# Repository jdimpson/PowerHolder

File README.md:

# PowerHolder PCB

Another variation of the AdaFruit PowerBoost 1000C (https://www.adafruit.com/product/2465) adapted for Raspberry Pi Zero. This is functionally similar to the PowerBoard (https://github.com/jdimpson/PowerBoard), but this time, with a side car that holds an entire 18650 Lithium Ion cell. As with PowerBoard, adds a  schottkey diode and programmable tactile button and LED and patches the Low Battery (LBO) signal to the Pi via a level shifter.

Also significant, this board lets you choose whether you want to pick-and-place and then reflow your own electronic components, or just go out and buy a PowerBoost 1000C from AdaFruit. You still have to solder on a diode, the battery holder clips, and (if you want them) the signal LED, programmable button, enable switch, and the level shifting mosfet for the LBO signal. But most of the fiddly parts, notably the U1 and U2 controller chips, you can use from the standard AdaFruit product. Just solder the board into place in the matching header holes with the male header pins they provide, or get some female headers too (that option makes clearance problems).

Note: when you solder a Powerboost in place, it's JST socket won't be accessible. Presumably this is okay because the battery sidecar is right there. The drawback is that the sidecar assumes your 18650 cell has exposed electrical contact on each of the opposing ends of the cell cylinder, rather than wires or tabs spot-welded onto the battery then brought out to a JST or similar connector. You could cut off the connector and solder battery wires onto the BAT and GND pins of the header if you want, or to the plus and minus pads of the battery clips.

Other things worthy of note:
- The MicroUSB connector is not the same foot print as AdaFruit uses in their PowerBoost, because I couldn't figure out which part which part number it was. My chosen replacement still has the through-hole-ish studs for physical reinforcement like Adafruit uses, but the footprints are incompatible.
- A BOM export is provided, which contains Digi-Key part numbers as wellas vendor part numbers.
- Python software that works with the LBO signal, button, and LED are available in the [RPiIoT](https://github.com/jdimpson/RPiIoT) repo. You don't have to use this software to benefit from this board, but you do want to monitor GPIO26/Phy37 because when it goes low, the battery voltage has dropped near the point where the charge controller will soon switch off power.
- Auxillary header is provided for USB/5VDC electrical input if you don't want to use MicroUSB.
- Auxillary header is provided for boosted 5VDC electrical output if you want to power something else with this board (in addition to, or instead of, an RPi Zero). NOte this auxillary output is not protected by the schottkey diode. This is analogous to the USB output header that the original PowerBoost 1000C provides, although the sense resistors used to indicate availability of > 500 mA have been removed.
- Unlike most RPi Zero daughter boards (hats, although this does not qualify as a hat because it has no EEPROM and is larger than the starndard board footprint), this board makes more sense to mount _underneath_ the RPi Zero. You'd do this by soldering female headers into the bottom of the RPi Zero, or better yet, the stacking headers like this: https://www.adafruit.com/product/2223. THen put male headers on the PowerHolder, stack the Zero on the PowerHolder, and then put whatever you want on top of the Zero as normal. You can also put the PowerHolder on top of the Zero (with or without stacking header) but the battery placement make the whole thing look weird to me.
- The PowerBoost 1000C can source about 1 Amp of current. This is plenty for an RPi Zero, with enough to spare for a camera and another hat of some type. It might even be enough to power an RPi 1 plus or 2, and it will boot a 3 but you'll likely see warnings abou undercurrent conditions. It won't run a 3+ or a 4 (well, they say the 4 will adjust power usage, but I don't know if it adapts to as low as an amp, and I wouldn't want to waste a 4 in a low power configuration anyways). It also won't run a servo or other motor, because they seem to have such rapid current draw that the RPi Zero will reboot regularly, presumably due to voltage drop.

Changes 
- v1.01: Changed MicroUSB connector to one I can find on Digikey; move battery terminals further from RPi header; used thinner/narrower battery holder; add more plus and minus signs (near battery and the USB input header); improve location of component names; added circles around all used pins (squares around GND). 

TODO 
- Since the battery is now onboard, Figure out how to use NTC resistor ("THERM" in the schematic) to monitor battery temperature. This board provides a header to place the NTC, although I haven't experimented with it so have no recommendation for part to use.

Raspberry Pi Pins used:

- GPIO17/Phy11 is connected to a momentary / tactile switch. Available for arbitrary software control (typically running my powerboard.py and associated code from the [RPiIoT](https://github.com/jdimpson/RPiIoT) repo).
- GPIO27/Phy13 is connected to a resistor and then an LED. Available for arbitrary software control (e.g. flashing to show grace period, and typically running my powerboard.py and associated code from the [RPiIoT](https://github.com/jdimpson/RPiIoT) repo).
- GPIO26/Phy37 is connected to via transistor and appropriate hold up resistor to the LBO signal of the PowerBoost circuit. This is how the Raspberry Pi knows to shut down. The signal is held at battery level (but level shifted to 3.3 V before hitting the RPi) until the Li Ion battery level drops below 3.4VDC (or maybe it's 3.2V, I forget) at which point the LBO signal drops to ground. This tells the software on the RPi to do a graceful shutdown.

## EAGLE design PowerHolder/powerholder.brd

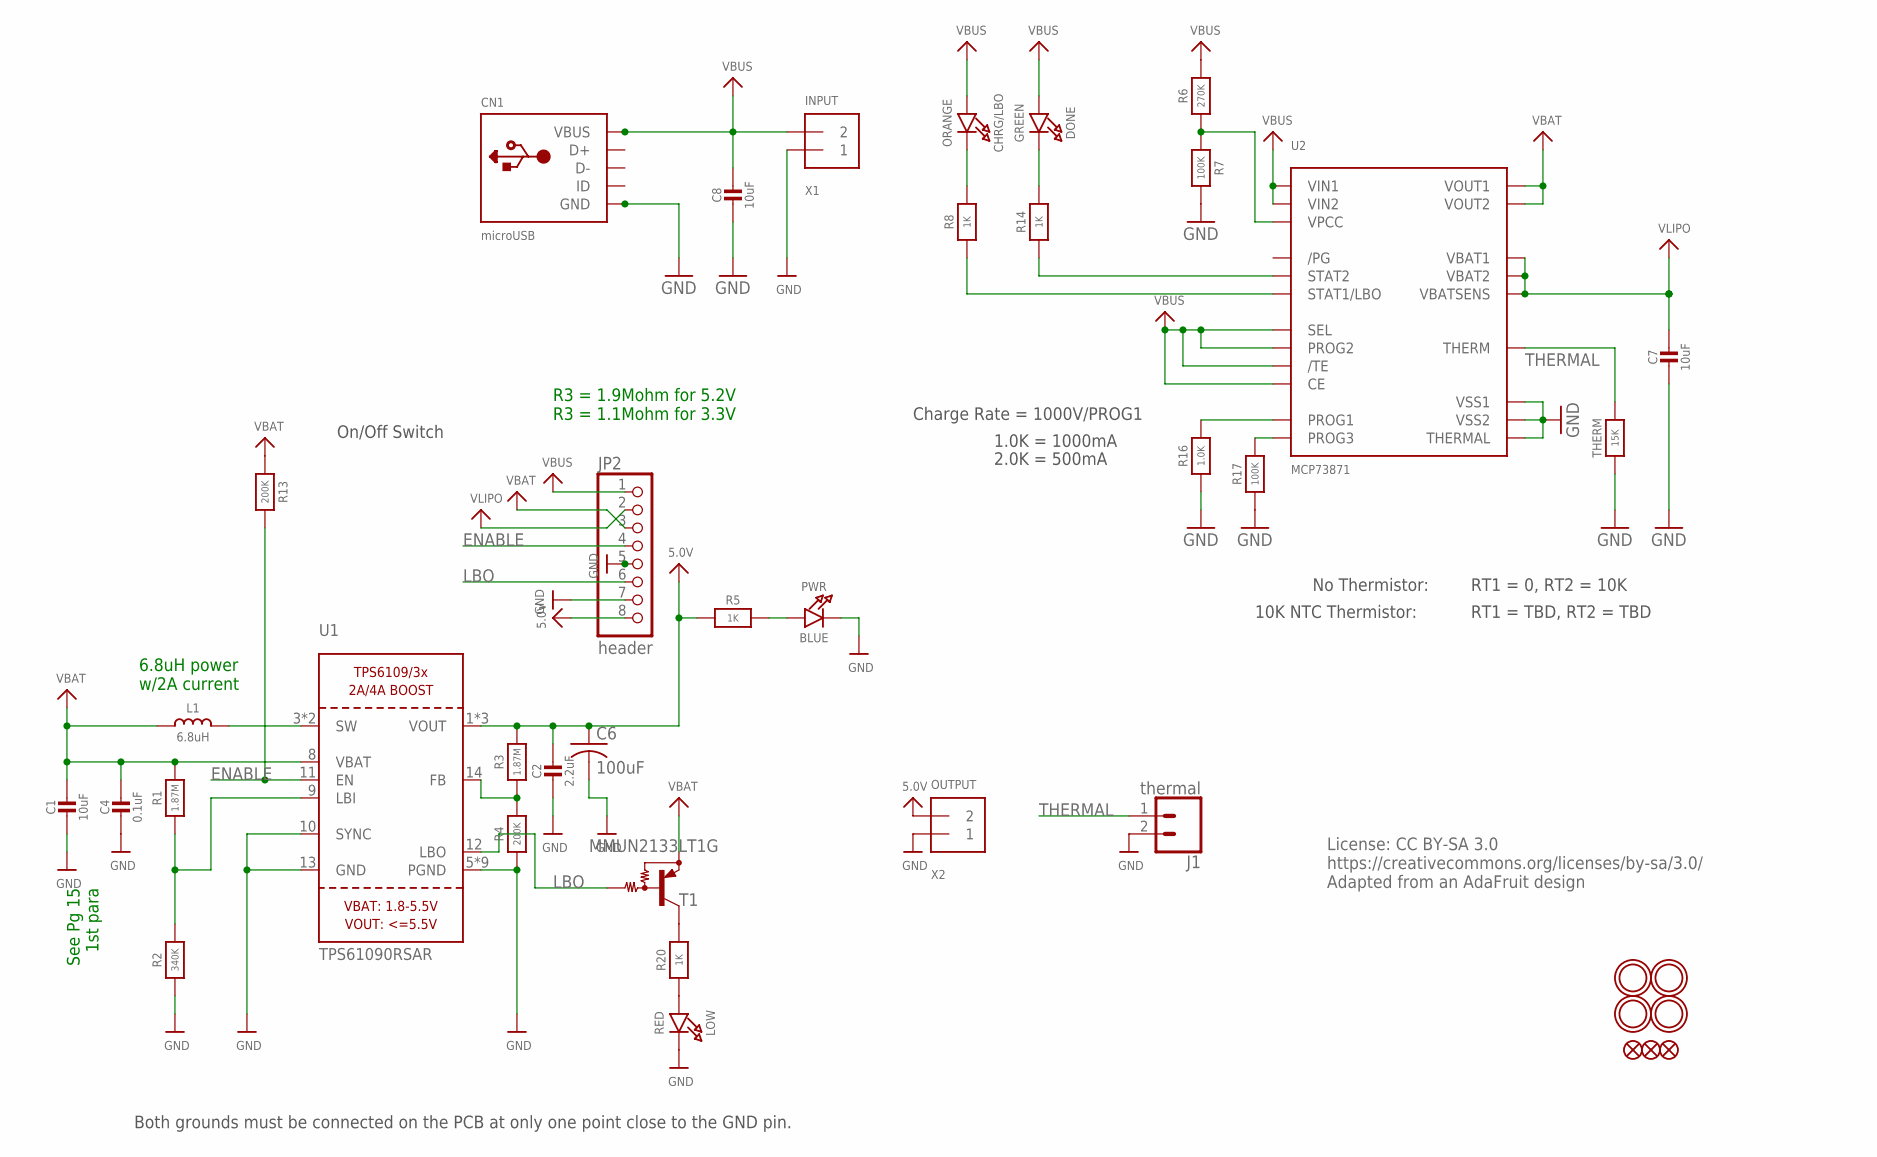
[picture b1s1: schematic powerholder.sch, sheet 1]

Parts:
C1, C7, C8: 10uF; 0805-NO@1
C2: 2.2uF; 0805-NO@1
C4: 0.1uF; 0805_10MGAP
C6: 100uF; C1210
CHRG/LBO: ORANGE; CHIPLED_0805_NOOUTLINE
CN1: microUSB; 4UCONN_20329
DONE: GREEN; CHIPLED_0805_NOOUTLINE
FID1, FID2, FID3: FIDUCIAL""; FIDUCIAL_1MM
J1: thermal; 1X02_NO_SILK
JP2: header; 1X08_ROUND
L1: 6.8uH; INDUCTOR_5X5MM_TDK_VLC5045
LOW: RED; CHIPLED_0805_NOOUTLINE
PWR: BLUE; CHIPLED_0805_NOOUTLINE
R1: 1.87M; _0805MP
R2: 340K; _0805MP
R3: 1.87M; 0805-NO
R4, R13: 200K; 0805-NO
R5, R8, R14, R20: 1K; 0805-NO
R6: 270K; 0805-NO
R7, R17: 100K; 0805-NO
R16: 1.0K; 0805-NO
T1: MMUN2133LT1G; SC59-BEC
THERM: 15K; 0805-NO
U1: TPS61090RSAR; PVQFN-16
U2: MCP73871; QFN20_4MM
U$10, U$11, U$50, U$51: MOUNTINGHOLE2.5; MOUNTINGHOLE_2.5_PLATED
X1: INPUT; TERMBLOCK_1X2-3.5MM
X2: OUTPUT; TERMBLOCK_1X2-3.5MM

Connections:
5.0V: C2.1, C6.1, JP2.8, R3.2, R5.1, U1.1 (VOUT), U1.15 (VOUT), U1.16 (VOUT), X2.2; also elsewhere on the board
ENABLE: JP2.4, R13.2, U1.11 (EN); also elsewhere on the board
GND: C1.2, C2.2, C4.2, C6.2, C7.2, C8.2, CN1.BASE@1 (GND), CN1.BASE@2 (GND), CN1.GND, CN1.SPRT@1 (GND), CN1.SPRT@2 (GND), CN1.SPRT@3 (GND), CN1.SPRT@4 (GND), J1.2, JP2.5, JP2.7, LOW.C, PWR.C, R2.1, R4.1, R7.2, R16.1, R17.1, THERM.1, U1.5 (PGND), U1.6 (PGND), U1.7 (PGND), U1.10 (SYNC), U1.13 (GND), U1.P$18 (PGND), U1.P$19 (PGND), U1.P$20 (PGND), U1.P$21 (PGND), U1.P$22 (PGND), U1.THERMAL (PGND), U2.P$10 (VSS1), U2.P$11 (VSS2), U2.P$21 (THERMAL), X1.1, X2.1; also elsewhere on the board
LBO: JP2.6, T1.B, U1.12 (LBO); also elsewhere on the board
unnamed: L1.P$2 (2), U1.3 (SW), U1.4 (SW)
unnamed: LOW.A, R20.1
unnamed: R1.1, R2.2, U1.9 (LBI)
unnamed: PWR.A, R5.2
unnamed: R3.1, R4.2, U1.14 (FB)
unnamed: R20.2, T1.C
unnamed: R6.1, R7.1, U2.P$2 (VPCC)
unnamed: DONE.C, R14.2
unnamed: R14.1, U2.P$7 (STAT2)
unnamed: R8.1, U2.P$8 (STAT1/LBO)
unnamed: CHRG/LBO.C, R8.2
unnamed: R17.2, U2.P$12 (PROG3)
unnamed: R16.2, U2.P$13 (PROG1)
THERMAL: J1.1, THERM.2, U2.P$5 (THERM)
VBAT: C1.1, C4.1, JP2.3, L1.P$1 (1), R1.2, R13.1, T1.E, U1.8 (VBAT), U2.P$1 (VOUT1), U2.P$20 (VOUT2); also elsewhere on the board
VBUS: C8.1, CHRG/LBO.A, CN1.VBUS, DONE.A, JP2.1, R6.2, U2.P$3 (SEL), U2.P$4 (PROG2), U2.P$9 (/TE), U2.P$17 (CE), U2.P$18 (VIN1), U2.P$19 (VIN2), X1.2
VLIPO: C7.1, JP2.2, U2.P$14 (VBAT1), U2.P$15 (VBAT2), U2.P$16 (VBATSENS); also elsewhere on the board

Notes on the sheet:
Both grounds must be connected on the PCB at only one point close to the GND pin.
On/Off Switch
See Pg 15 1st para
6.8uH power w/2A current
R3 = 1.9Mohm for 5.2V R3 = 1.1Mohm for 3.3V
Charge Rate = 1000V/PROG1
1.0K = 1000mA
2.0K = 500mA
No Thermistor:
10K NTC Thermistor:
RT1 = 0, RT2 = 10K
RT1 = TBD, RT2 = TBD
License: CC BY-SA 3.0 https://creativecommons.org/licenses/by-sa/3.0/ Adapted from an AdaFruit design

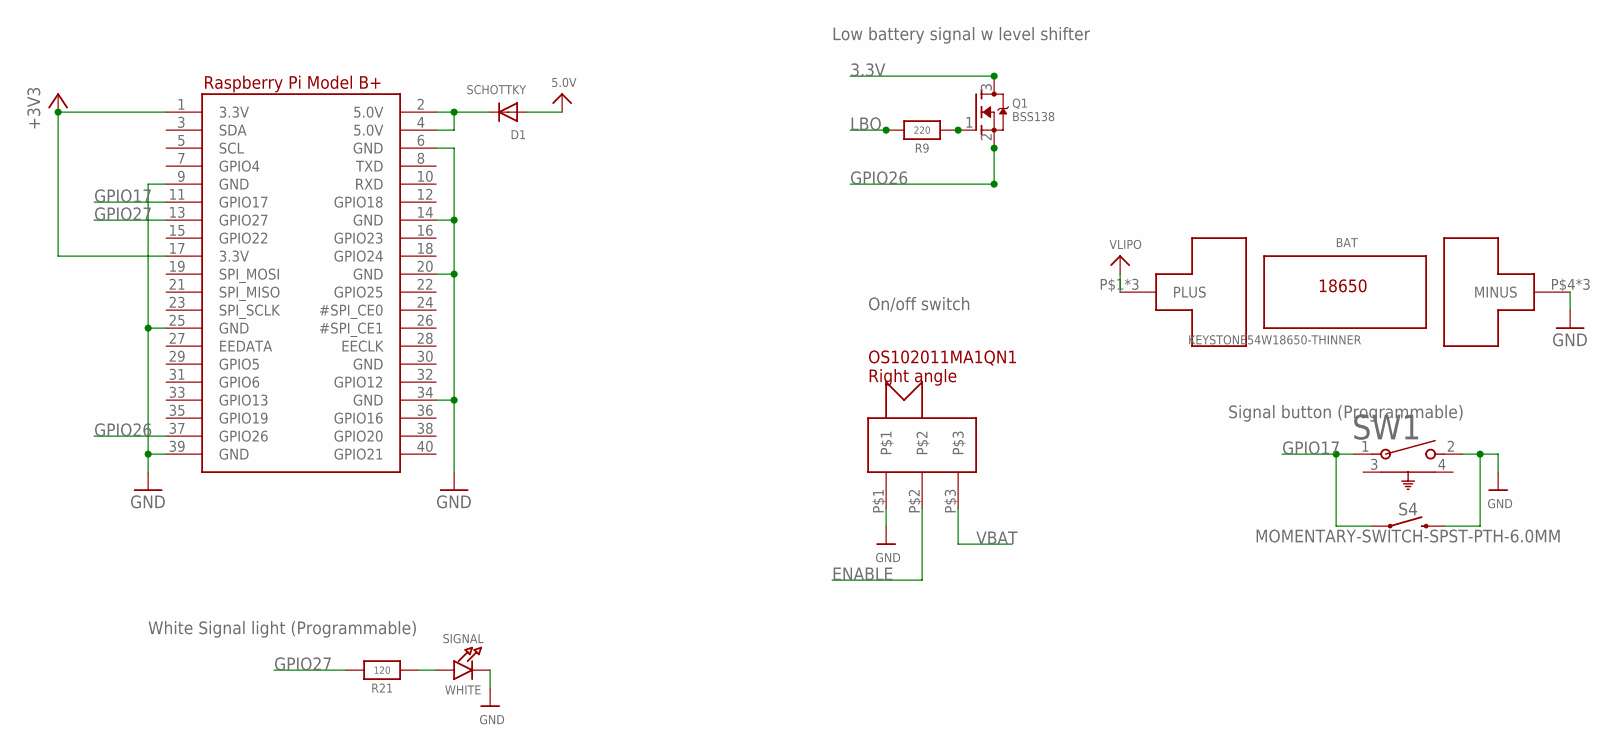
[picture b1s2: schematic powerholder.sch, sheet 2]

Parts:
BAT: KEYSTONE54W18650-THINNER
D1: SCHOTTKY; SOD-123FL
Q1: BSS138; SOT23-R
R9: 220; 0805-NO
R21: 120; 0805-NO
RPI1: RASPBERRYPI_BPLUS_BONNETNODIM; PI_BONNET_NODIM
S4: MOMENTARY-SWITCH-SPST-PTH-6.0MM; TACTILE_SWITCH_PTH_6.0MM
SIGNAL: WHITE; CHIPLED_0805_NOOUTLINE
SW1: 1825027-5; SW2_1825027-A
SW2: OS102011MA1QN1

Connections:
3.3V: Q1.3 (D), RPI1.1 (3.3V), RPI1.17 (3.3V)
5.0V: D1.A; also elsewhere on the board
5.0V@1: D1.C, RPI1.2 (5.0V), RPI1.4 (5.0V)
ENABLE: SW2.P$2; also elsewhere on the board
GND: BAT.P$4 (MINUS), BAT.P$5 (MINUS), BAT.P$6 (MINUS), RPI1.6 (GND), RPI1.9 (GND), RPI1.14 (GND), RPI1.20 (GND), RPI1.25 (GND), RPI1.30 (GND), RPI1.34 (GND), RPI1.39 (GND), S4.3 (2), SIGNAL.C, SW1.2, SW2.P$1; also elsewhere on the board
GPIO17: RPI1.11 (GPIO17), S4.1, SW1.1
GPIO26: Q1.2 (S), RPI1.37 (GPIO26)
GPIO27: R21.2, RPI1.13 (GPIO27)
LBO: R9.2; also elsewhere on the board
unnamed: Q1.1 (G), R9.1
unnamed: R21.1, SIGNAL.A
VBAT: SW2.P$3; also elsewhere on the board
VLIPO: BAT.P$1 (PLUS), BAT.P$2 (PLUS), BAT.P$3 (PLUS); also elsewhere on the board

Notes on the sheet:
Low battery signal w level shifter
On/off switch
Signal button (Programmable)
White Signal light (Programmable)

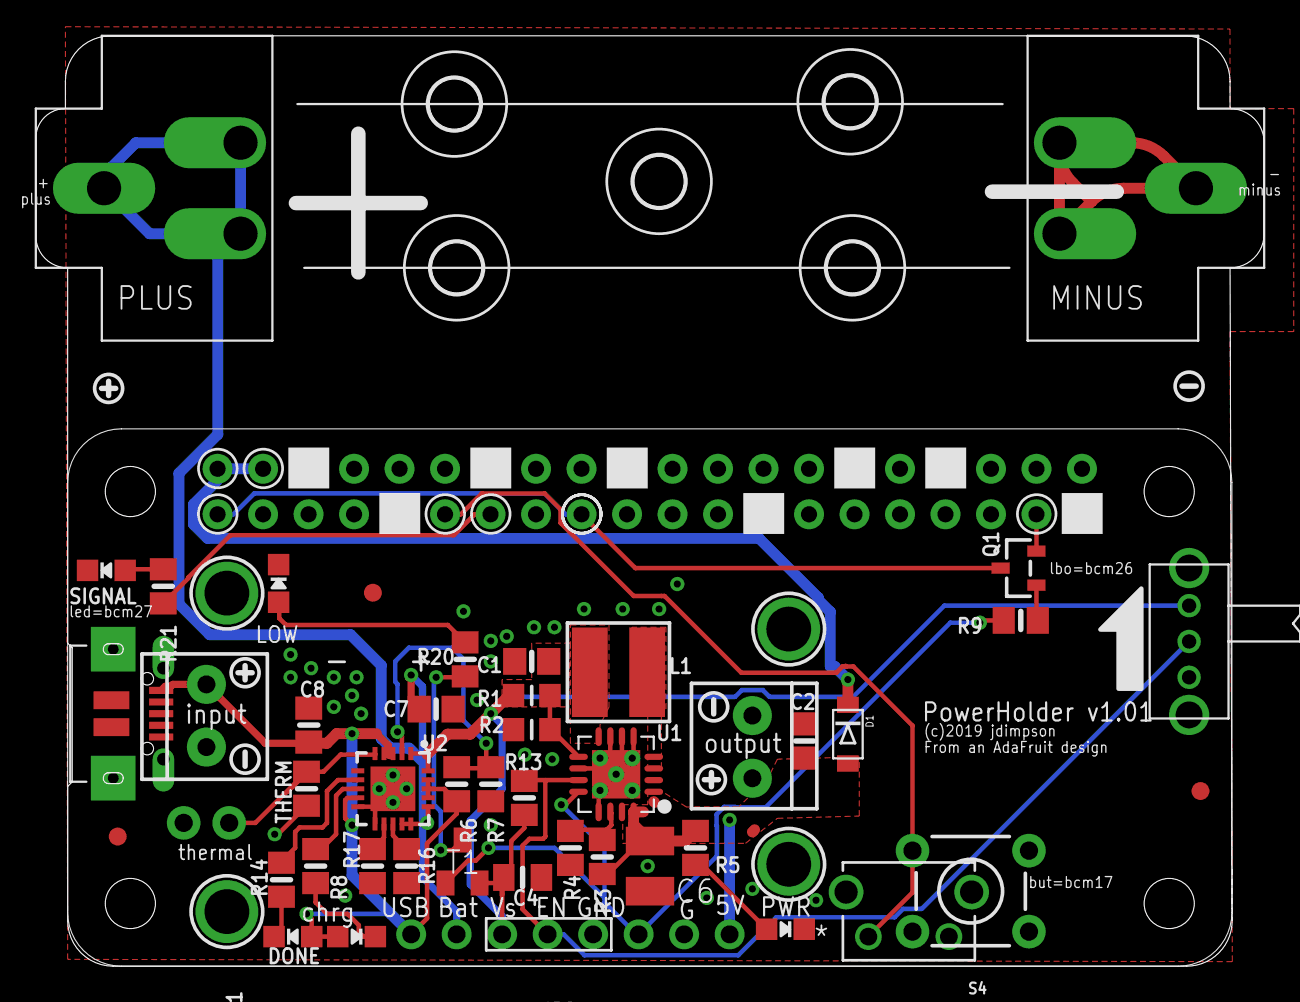
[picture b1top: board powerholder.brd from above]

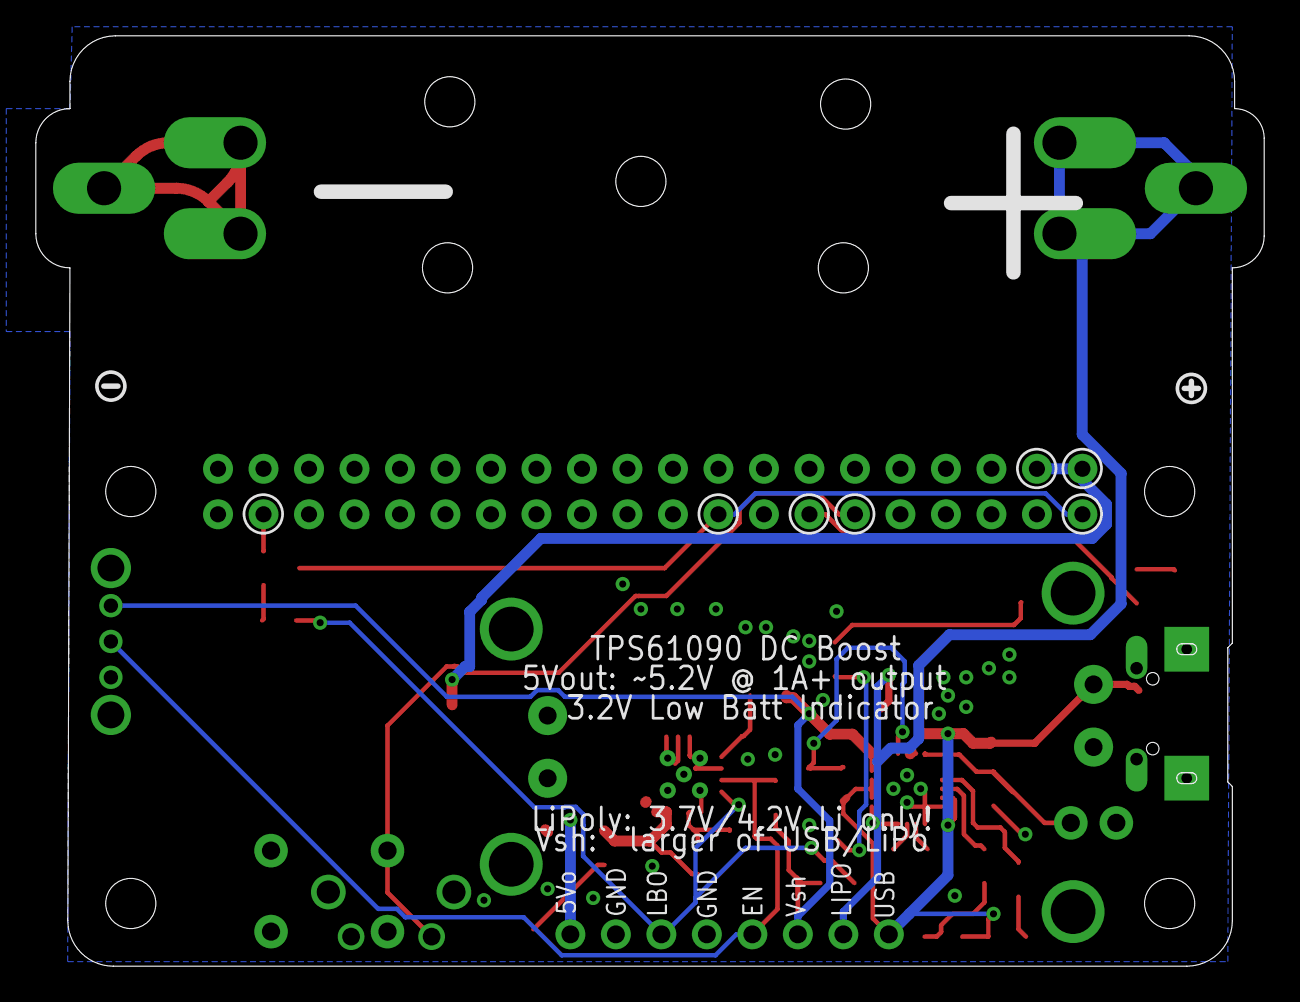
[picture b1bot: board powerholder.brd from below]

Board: 2 copper layers, 68.6 x 51.9 mm, 63 parts (2 on the bottom side), 28 nets.

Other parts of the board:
U$5, U$15, U$16, U$17, U$18: 2,8
U$12, U$28, U$53, U$54: SYMBOL_MINUS
U$21, U$22, U$45, U$52: SYMBOL_PLUS

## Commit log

2020-09-07 more blathering
2020-09-09 image of board
2020-09-09 link to image
2020-09-09 Linked to python repo
2020-09-24 Add that no JST socket is available
2020-09-24 More clarification
2020-09-24 Editing on github with Android suddenly introduces typos
2020-09-24 Add pin description
2020-09-24 Links

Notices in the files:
PowerHolder/powerholder.brd:
(c)2019 jdimpson
parts and their libraries:
microbuilder: This work is placed in the public domain, and may be freely used for commercial and non-commercial work with the following conditions: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
SparkFun-Switches: Licensing: Creative Commons ShareAlike 4.0 International - https://creativecommons.org/licenses/by-sa/4.0
